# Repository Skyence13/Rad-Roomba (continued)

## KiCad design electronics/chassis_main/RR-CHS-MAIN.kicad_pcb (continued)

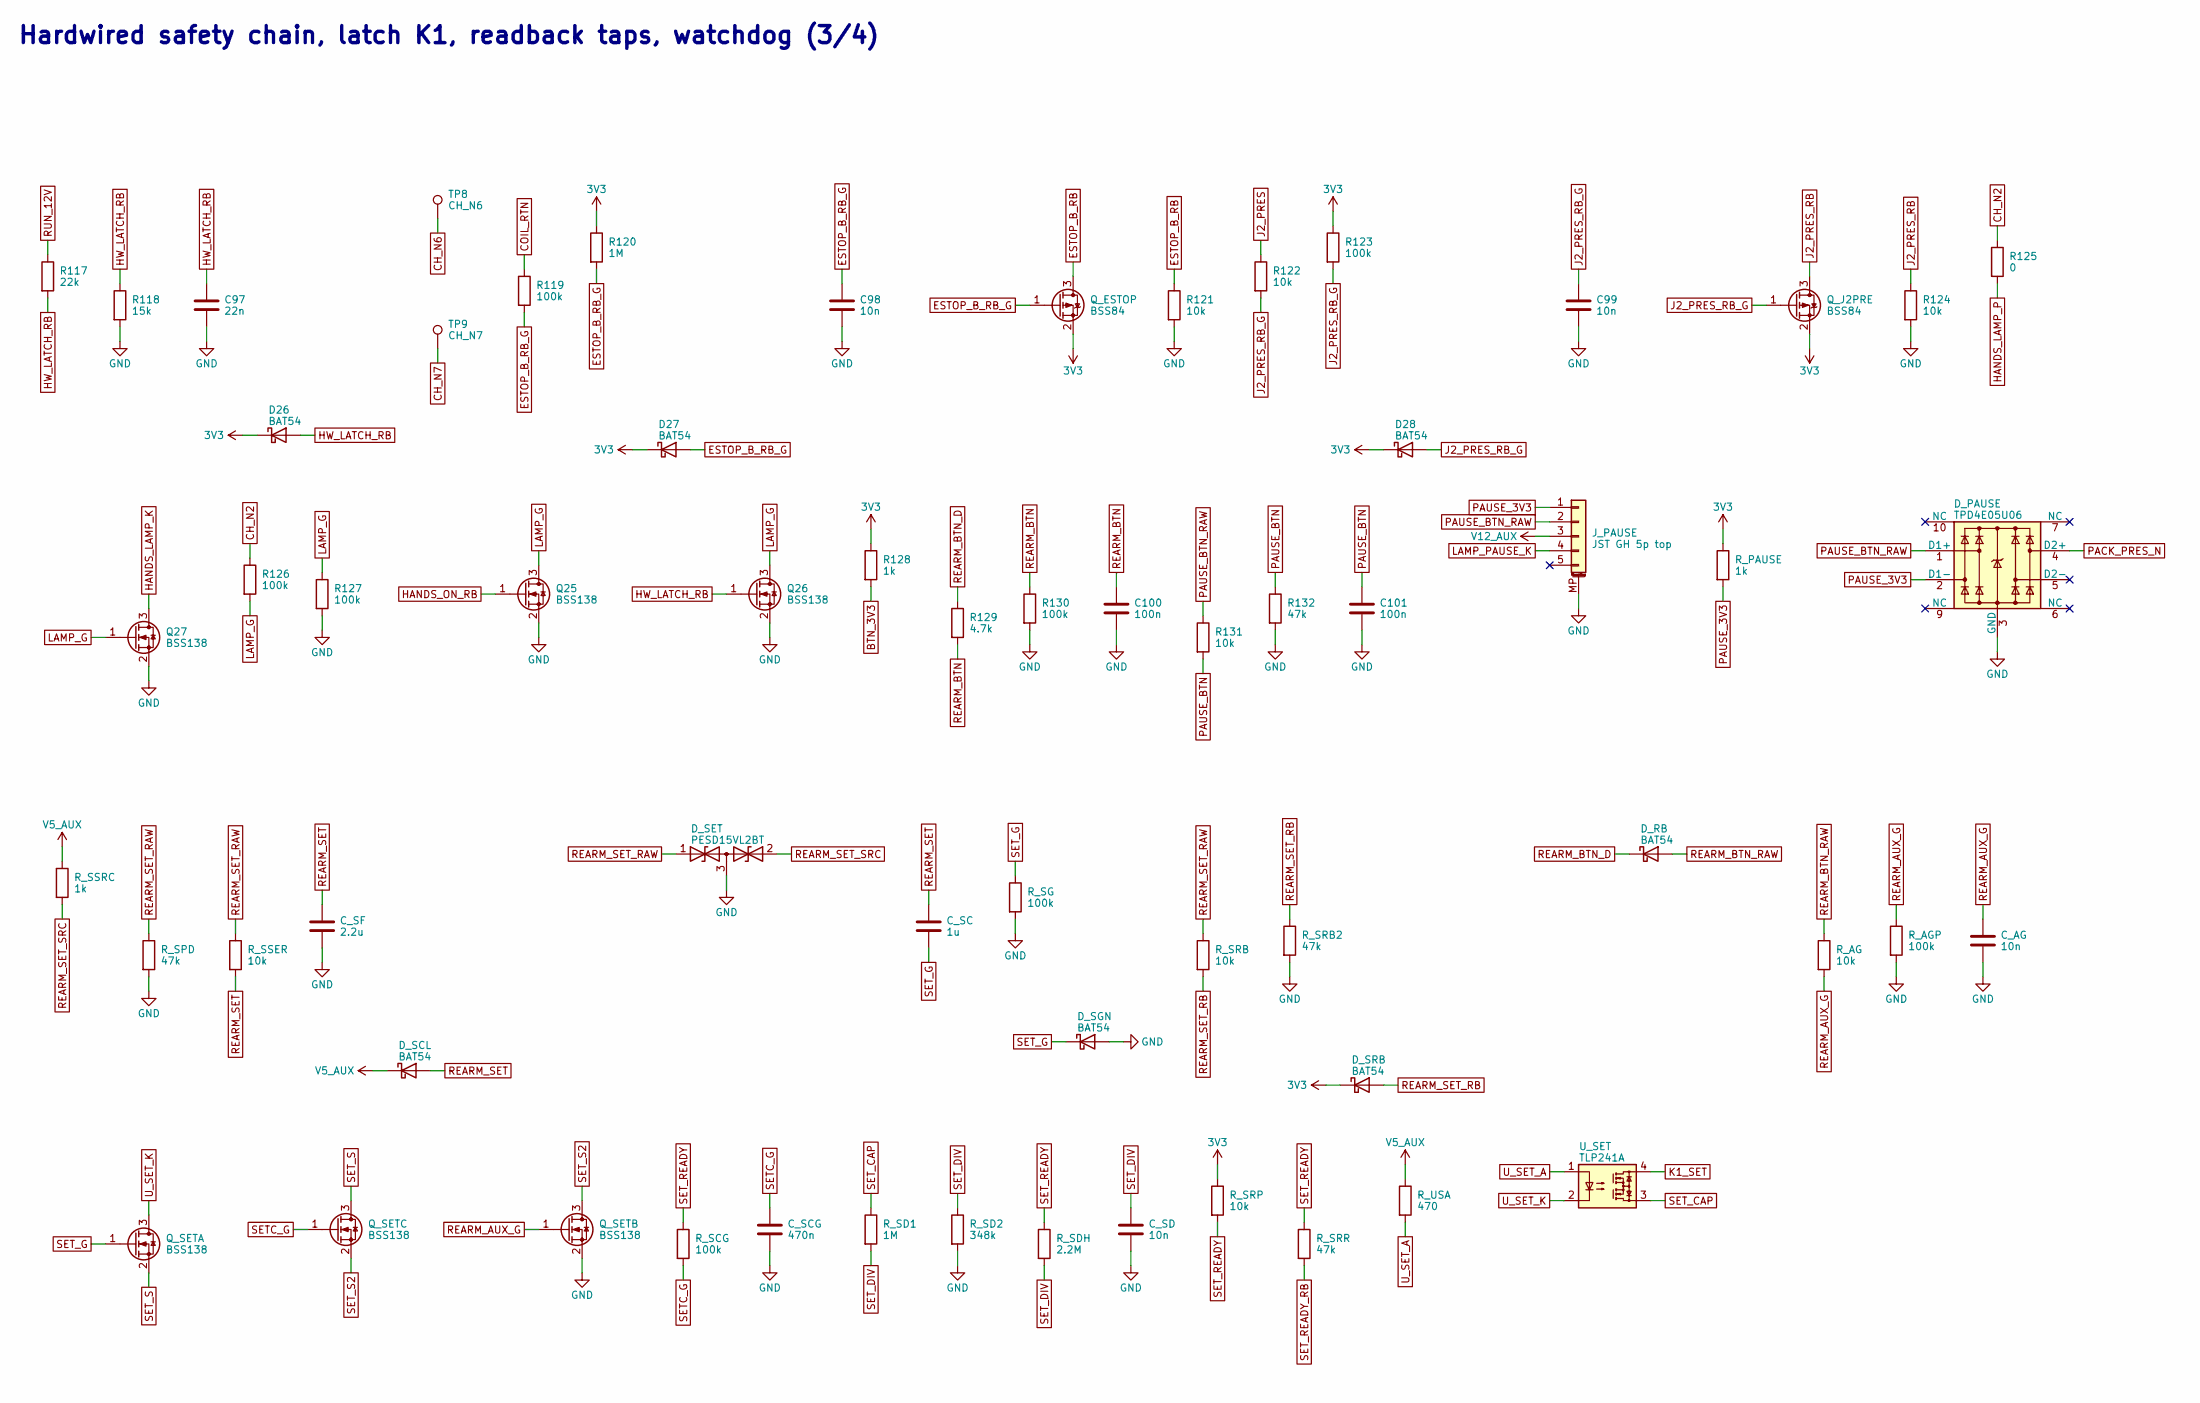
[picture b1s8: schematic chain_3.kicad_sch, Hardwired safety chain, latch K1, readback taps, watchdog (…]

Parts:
C97: 22n; C_0603_1608Metric; MPN CC0603KRX7R9BB223
C98, C99: 10n; C_0603_1608Metric; MPN CC0603KRX7R9BB103
C100, C101: 100n; C_0603_1608Metric; MPN CC0603KRX7R9BB104
C_AG: 10n; C_0603_1608Metric; MPN CC0603KRX7R9BB103
C_SC: 1u; C_0603_1608Metric; MPN GRM188R71C105KA12D
C_SCG: 470n; C_0603_1608Metric; MPN CC0603KRX7R7BB474
C_SD: 10n; C_0603_1608Metric; MPN CC0603KRX7R9BB103
C_SF: 2.2u; C_0603_1608Metric; MPN GRM188R71C225KE11D
D26, D27, D28: BAT54; D_SOD-123; MPN BAT54W-7-F
D_PAUSE: TPD4E05U06; USON-10_2.5x1.0mm_P0.5mm; MPN TPD4E05U06DQAR
D_RB: BAT54; D_SOD-123; MPN BAT54W-7-F
D_SCL: BAT54; D_SOD-123; MPN BAT54W-7-F
D_SET: PESD15VL2BT; SOT-23; MPN PESD15VL2BT,215
D_SGN: BAT54; D_SOD-123; MPN BAT54W-7-F
D_SRB: BAT54; D_SOD-123; MPN BAT54W-7-F
J_PAUSE: JST GH 5p top; JST_GH_BM05B-GHS-TBT_1x05-1MP_P1.25mm_Vertical; MPN BM05B-GHS-TBT(LF)(SN)
Q25, Q26, Q27: BSS138; SOT-23; MPN BSS138
Q_ESTOP: BSS84; SOT-23; MPN BSS84,215
Q_J2PRE: BSS84; SOT-23; MPN BSS84,215
Q_SETA: BSS138; SOT-23; MPN BSS138
Q_SETB: BSS138; SOT-23; MPN BSS138
Q_SETC: BSS138; SOT-23; MPN BSS138
R117: 22k; R_0603_1608Metric; MPN RC0603FR-0722KL
R118: 15k; R_0603_1608Metric; MPN RC0603FR-0715KL
R119, R123, R126, R127, R130: 100k; R_0603_1608Metric; MPN RC0603FR-07100KL
R120: 1M; R_0603_1608Metric; MPN RC0603FR-071ML
R121, R122, R124, R131: 10k; R_0603_1608Metric; MPN RC0603FR-0710KL
R125: 0; R_0603_1608Metric; MPN RC0603FR-070RL
R128: 1k; R_0603_1608Metric; MPN RC0603FR-071KL
R129: 4.7k; R_0603_1608Metric; MPN RC0603FR-074K7L
R132: 47k; R_0603_1608Metric; MPN RC0603FR-0747KL
R_AG: 10k; R_0603_1608Metric; MPN RC0603FR-0710KL
R_AGP: 100k; R_0603_1608Metric; MPN RC0603FR-07100KL
R_PAUSE: 1k; R_0603_1608Metric; MPN RC0603FR-071KL
R_SCG: 100k; R_0603_1608Metric; MPN RC0603FR-07100KL
R_SD1: 1M; R_0603_1608Metric; MPN RC0603FR-071ML
R_SD2: 348k; R_0603_1608Metric; MPN RC0603FR-07348KL
R_SDH: 2.2M; R_0603_1608Metric; MPN RC0603FR-072M2L
R_SG: 100k; R_0603_1608Metric; MPN RC0603FR-07100KL
R_SPD: 47k; R_0603_1608Metric; MPN RC0603FR-0747KL
R_SRB: 10k; R_0603_1608Metric; MPN RC0603FR-0710KL
R_SRB2: 47k; R_0603_1608Metric; MPN RC0603FR-0747KL
R_SRP: 10k; R_0603_1608Metric; MPN RC0603FR-0710KL
R_SRR: 47k; R_0603_1608Metric; MPN RC0603FR-0747KL
R_SSER: 10k; R_0603_1608Metric; MPN RC0603FR-0710KL
R_SSRC: 1k; R_0603_1608Metric; MPN RC0603FR-071KL
R_USA: 470; R_0603_1608Metric; MPN RC0603FR-07470RL
TP8: CH_N6; TestPoint_Keystone_5019_Miniature; MPN 5019
TP9: CH_N7; TestPoint_Keystone_5019_Miniature; MPN 5019
U_SET: TLP241A; SMDIP-4_W9.53mm; MPN TLP241A(TP1,F

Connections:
3V3: D26.1 (K), D27.1 (K), D28.1 (K), D_SRB.1 (K), Q_ESTOP.2 (S), Q_J2PRE.2 (S), R120.1, R123.1, R128.1, R_PAUSE.1, R_SRP.1; also elsewhere on the board
BTN_3V3: R128.2; also elsewhere on the board
CH_N2: R125.1, R126.1; also elsewhere on the board
CH_N6: TP8.1; also elsewhere on the board
CH_N7: TP9.1; also elsewhere on the board
COIL_RTN: R119.1; also elsewhere on the board
ESTOP_B_RB: Q_ESTOP.3 (D), R121.1; also elsewhere on the board
ESTOP_B_RB_G: C98.1, D27.2 (A), Q_ESTOP.1 (G), R119.2, R120.2
GND: C97.2, C98.2, C99.2, C100.2, C101.2, C_AG.2, C_SCG.2, C_SD.2, C_SF.2, D_PAUSE.3 (GND), D_PAUSE.8 (GND), D_SET.3 (common), D_SGN.2 (A), J_PAUSE.MP (MountPin), Q25.2 (S), Q26.2 (S), Q27.2 (S), Q_SETB.2 (S), R118.2, R121.2, R124.2, R127.2, R130.2, R132.2, R_AGP.2, R_SD2.2, R_SG.2, R_SPD.2, R_SRB2.2; also elsewhere on the board
HANDS_LAMP_K: Q27.3 (D); also elsewhere on the board
HANDS_LAMP_P: R125.2; also elsewhere on the board
HANDS_ON_RB: Q25.1 (G); also elsewhere on the board
HW_LATCH_RB: C97.1, D26.2 (A), Q26.1 (G), R117.2, R118.1; also elsewhere on the board
J2_PRES: R122.1; also elsewhere on the board
J2_PRES_RB: Q_J2PRE.3 (D), R124.1; also elsewhere on the board
J2_PRES_RB_G: C99.1, D28.2 (A), Q_J2PRE.1 (G), R122.2, R123.2
K1_SET: U_SET.4; also elsewhere on the board
LAMP_G: Q25.3 (D), Q26.3 (D), Q27.1 (G), R126.2, R127.1
LAMP_PAUSE_K: J_PAUSE.4; also elsewhere on the board
PACK_PRES_N: D_PAUSE.4 (D2+); also elsewhere on the board
PAUSE_3V3: D_PAUSE.2 (D1-), J_PAUSE.1, R_PAUSE.2
PAUSE_BTN: C101.1, R131.2, R132.1; also elsewhere on the board
PAUSE_BTN_RAW: D_PAUSE.1 (D1+), J_PAUSE.2, R131.1
REARM_AUX_G: C_AG.1, Q_SETB.1 (G), R_AG.2, R_AGP.1
REARM_BTN: C100.1, R129.2, R130.1; also elsewhere on the board
REARM_BTN_D: D_RB.1 (K), R129.1
REARM_BTN_RAW: D_RB.2 (A), R_AG.1; also elsewhere on the board
REARM_SET: C_SC.1, C_SF.1, D_SCL.2 (A), R_SSER.2
REARM_SET_RAW: D_SET.1 (A1), R_SPD.1, R_SRB.1, R_SSER.1; also elsewhere on the board
REARM_SET_RB: D_SRB.2 (A), R_SRB.2, R_SRB2.1; also elsewhere on the board
REARM_SET_SRC: D_SET.2 (A2), R_SSRC.2; also elsewhere on the board
RUN_12V: R117.1; also elsewhere on the board
SETC_G: C_SCG.1, Q_SETC.1 (G), R_SCG.2
SET_CAP: R_SD1.1, U_SET.3; also elsewhere on the board
SET_DIV: C_SD.1, R_SD1.2, R_SD2.1, R_SDH.2; also elsewhere on the board
SET_G: C_SC.2, D_SGN.1 (K), Q_SETA.1 (G), R_SG.1
SET_READY: R_SCG.1, R_SDH.1, R_SRP.2, R_SRR.1; also elsewhere on the board
SET_READY_RB: R_SRR.2; also elsewhere on the board
SET_S: Q_SETA.2 (S), Q_SETC.3 (D)
SET_S2: Q_SETB.3 (D), Q_SETC.2 (S)
U_SET_A: R_USA.2, U_SET.1
U_SET_K: Q_SETA.3 (D), U_SET.2; also elsewhere on the board
V5_AUX: D_SCL.1 (K), R_SSRC.1, R_USA.1; also elsewhere on the board
V12_AUX: J_PAUSE.3; also elsewhere on the board

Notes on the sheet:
Hardwired safety chain, latch K1, readback taps, watchdog (3/4)

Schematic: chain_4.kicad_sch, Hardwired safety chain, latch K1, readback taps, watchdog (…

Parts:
C_KR: 22n; C_0603_1608Metric; MPN CC0603KRX7R9BB223
C_LB1, C_LB2: 100n; C_0603_1608Metric; MPN CC0603KRX7R9BB104
C_N6A: 22n; C_0603_1608Metric; MPN CC0603KRX7R9BB223
C_NC: 10n; C_0603_1608Metric; MPN CC0603KRX7R9BB103
C_SDB: 1u; C_0603_1608Metric; MPN GRM188R71C105KA12D
C_U9T: 22n; C_0603_1608Metric; MPN CC0603KRX7R9BB223
C_U46, C_U47: 100n; C_0603_1608Metric; MPN CC0603KRX7R9BB104
D_AUX: PESD15VL2BT; SOT-23; MPN PESD15VL2BT,215
D_HR: 1N4148W; D_SOD-123; MPN 1N4148W-7-F
D_K1B: BAT54; D_SOD-123; MPN BAT54W-7-F
D_KR: BAT54; D_SOD-123; MPN BAT54W-7-F
D_LSR: 1N4148W; D_SOD-123; MPN 1N4148W-7-F
D_N6A: BAT54; D_SOD-123; MPN BAT54W-7-F
D_NC: BAT54; D_SOD-123; MPN BAT54W-7-F
D_RSET: 1N4148W; D_SOD-123; MPN 1N4148W-7-F
D_RUN: S1G; D_SMA; MPN S1G-13-F
D_U9T: BAT54; D_SOD-123; MPN BAT54W-7-F
Q_HSET: BSS84; SOT-23; MPN BSS84,215
Q_LB: BSS138; SOT-23; MPN BSS138
Q_LTA: BSS138; SOT-23; MPN BSS138
Q_LTB: BSS138; SOT-23; MPN BSS138
Q_SDIS: BSS138; SOT-23; MPN BSS138
Q_SDISB: BSS138; SOT-23; MPN BSS138
R_21BA: 680; R_0603_1608Metric; MPN RC0603FR-07680RL
R_GA5, R_GA7: 47k; R_0603_1608Metric; MPN RC0603FR-0747KL
R_GB7: 47k; R_0603_1608Metric; MPN RC0603FR-0747KL
R_HA: 1.5k; R_1206_3216Metric; MPN RC1206FR-071K5L
R_HS: 470; R_0603_1608Metric; MPN RC0603FR-07470RL
R_K1B: 47k; R_0603_1608Metric; MPN RC0603FR-0747KL
R_KR1: 100k; R_0603_1608Metric; MPN RC0603FR-07100KL
R_KR2: 56k; R_0603_1608Metric; MPN RC0603FR-0756KL
R_LB1, R_LB3: 10k; R_0603_1608Metric; MPN RC0603FR-0710KL
R_LB2: 30.9k; R_0603_1608Metric; MPN RC0603FR-0730K9L
R_LBG: 100k; R_0603_1608Metric; MPN RC0603FR-07100KL
R_LBR: 47k; R_0603_1608Metric; MPN RC0603FR-0747KL
R_LSA: 1.5k; R_1206_3216Metric; MPN RC1206FR-071K5L
R_LTA: 100k; R_0603_1608Metric; MPN RC0603FR-07100KL
R_LTB: 100k; R_0603_1608Metric; MPN RC0603FR-07100KL
R_N6A1: 100k; R_0603_1608Metric; MPN RC0603FR-07100KL
R_N6A2: 56k; R_0603_1608Metric; MPN RC0603FR-0756KL
R_NC1: 47k; R_0603_1608Metric; MPN RC0603FR-0747KL
R_NC2: 1M; R_0603_1608Metric; MPN RC0603FR-071ML
R_RHD: 10k; R_0603_1608Metric; MPN RC0603FR-0710KL
R_SDB1: 100k; R_0603_1608Metric; MPN RC0603FR-07100KL
R_SDB2: 56k; R_0603_1608Metric; MPN RC0603FR-0756KL
R_SDG: 100k; R_0603_1608Metric; MPN RC0603FR-07100KL
R_SDIS: 1k; R_1206_3216Metric; MPN RC1206FR-071KL
R_SV2, R_SV3, R_SV4, R_SV5, R_SV6, R_SV7, R_SV8, R_SV9, R_SV10: 220k; R_0603_1608Metric; MPN RC0603FR-07220KL
R_U9T1: 100k; R_0603_1608Metric; MPN RC0603FR-07100KL
R_U9T2: 56k; R_0603_1608Metric; MPN RC0603FR-0756KL
R_USK: 100k; R_0603_1608Metric; MPN RC0603FR-07100KL
R_WDPD: 10k; R_0603_1608Metric; MPN RC0603FR-0710KL
U21B: TLP241A; SMDIP-4_W9.53mm; MPN TLP241A(TP1,F
U46: TLV3201; SOT-23-5; MPN TLV3201AIDBVR
U_HOLD: TLP241A; SMDIP-4_W9.53mm; MPN TLP241A(TP1,F
U_LS: TLP241A; SMDIP-4_W9.53mm; MPN TLP241A(TP1,F

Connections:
3V3: C_U47.1, D_K1B.2 (A), D_KR.1 (K), D_N6A.1 (K), D_NC.1 (K), D_U9T.1 (K), R_SDG.1; also elsewhere on the board
BTN_3V3: D_AUX.2 (A2); also elsewhere on the board
CHAIN_END: D_RSET.2 (A), R_SDB1.1, R_SV2.1; also elsewhere on the board
CHN6A_RB: C_N6A.1, D_N6A.2 (A), R_N6A1.2, R_N6A2.1; also elsewhere on the board
CH_N6: U21B.4; also elsewhere on the board
CH_N6A: R_N6A1.1, R_SV9.1, U21B.3; also elsewhere on the board
COIL_RTN: U_LS.4; also elsewhere on the board
GND: C_KR.2, C_LB1.2, C_LB2.2, C_N6A.2, C_NC.2, C_SDB.2, C_U9T.2, C_U46.2, C_U47.2, D_AUX.3 (common), D_HR.2 (A), D_LSR.2 (A), Q_LB.2 (S), Q_LTA.2 (S), Q_LTB.2 (S), Q_SDIS.2 (S), Q_SDISB.2 (S), R_KR2.2, R_LB3.2, R_LBG.2, R_LTA.2, R_LTB.2, R_N6A2.2, R_NC2.2, R_RHD.2, R_SDB2.2, R_U9T2.2, R_WDPD.2, U46.2 (V-), U_HOLD.2, U_LS.2; also elsewhere on the board
HEAD_LOOP2_OK: Q_LB.1 (G), R_LBG.1, R_LBR.1, U46.1 (OUT)
HEAD_LOOP2_OK_RB: R_LBR.2; also elsewhere on the board
HEAD_LOOP_OK_IO: R_GA5.2; also elsewhere on the board
HEAD_LOOP_OK_RB: R_GA5.1; also elsewhere on the board
HOLD_A: D_HR.1 (K), R_HA.2, R_HS.2, R_SV7.1, U_HOLD.1
HSET_D: Q_HSET.3 (D), R_HS.1
HW_LATCH_G: C_U9T.1, D_U9T.2 (A), R_U9T1.2, R_U9T2.1; also elsewhere on the board
K1_BIAS: D_K1B.1 (K), R_K1B.1
K1_NC1: R_NC1.1; also elsewhere on the board
K1_RUN: R_KR1.1, R_SV3.1, U_HOLD.3; also elsewhere on the board
K1_SEAL_A: R_K1B.2; also elsewhere on the board
LAB_KEY_N_IO: R_GA7.2; also elsewhere on the board
LAB_KEY_N_RB: R_GA7.1; also elsewhere on the board
LATCH_NC_RB: C_NC.1, D_NC.2 (A), R_NC1.2, R_NC2.1; also elsewhere on the board
LATCH_RUN_RB: C_KR.1, D_KR.2 (A), R_KR1.2, R_KR2.1; also elsewhere on the board
LOOP_F: Q_LTA.3 (D); also elsewhere on the board
LOOP_FB: C_LB1.1, Q_LTB.3 (D), R_LB1.2, U46.3 (IN+)
LOOP_SNS: R_LB1.1; also elsewhere on the board
LOOP_TEST_A: Q_LTA.1 (G), R_LTA.1; also elsewhere on the board
LOOP_TEST_B: Q_LTB.1 (G), R_LTB.1; also elsewhere on the board
LOOP_VB: C_LB2.1, R_LB2.2, R_LB3.1, U46.4 (IN-)
LS_A: D_LSR.1 (K), R_LSA.2, R_SV8.1, U_LS.1
REARM_BTN_RAW: D_AUX.1 (A1); also elsewhere on the board
RELAY_RTN: R_SV6.1, U_LS.3; also elsewhere on the board
RSET_A: D_RSET.1 (K); also elsewhere on the board
RUN_12V: D_RUN.1 (K), R_SV5.1; also elsewhere on the board
RUN_HD: D_RUN.2 (A), R_HA.1, R_LSA.1, R_RHD.1, R_SV4.1, R_U9T1.1, U_HOLD.4; also elsewhere on the board
SDISB_G: C_SDB.1, Q_SDISB.1 (G), R_SDB1.2, R_SDB2.1
SDIS_G: Q_SDIS.1 (G), Q_SDISB.3 (D), R_SDG.2
SET_CAP: R_SDIS.1, R_SV10.1; also elsewhere on the board
SET_DIS: Q_SDIS.3 (D), R_SDIS.2
SVC_CHAIN_END: R_SV2.2; also elsewhere on the board
SVC_CH_N6A: R_SV9.2; also elsewhere on the board
SVC_HOLD_A: R_SV7.2; also elsewhere on the board
SVC_K1_RUN: R_SV3.2; also elsewhere on the board
SVC_LS_A: R_SV8.2; also elsewhere on the board
SVC_RELAY_RTN: R_SV6.2; also elsewhere on the board
SVC_RUN_12V: R_SV5.2; also elsewhere on the board
SVC_RUN_HD: R_SV4.2; also elsewhere on the board
SVC_SET_CAP: R_SV10.2; also elsewhere on the board
U21B_A: R_21BA.2, U21B.1
U21B_K: Q_LB.3 (D), U21B.2
U_SET_K: Q_HSET.1 (G), R_USK.2; also elsewhere on the board
V5_AUX: C_U46.1, Q_HSET.2 (S), R_21BA.1, R_LB2.1, R_USK.1, U46.5 (V+); also elsewhere on the board
WDG_STROBE: R_GB7.1, R_WDPD.1; also elsewhere on the board
WDG_STROBE_IO: R_GB7.2; also elsewhere on the board

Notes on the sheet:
Hardwired safety chain, latch K1, readback taps, watchdog (4/4)

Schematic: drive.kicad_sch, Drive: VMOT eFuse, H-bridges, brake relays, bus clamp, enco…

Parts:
C102, C112, C119, C120: 1n; C_0603_1608Metric; MPN CC0603JRNPO9BN102
C103, C104, C113: 10n; C_0603_1608Metric; MPN CC0603KRX7R9BB103
C105, C106, C107: 270u; CP_Elec_10x10.5; MPN EEHZA1V271P
C108, C109, C110, C111, C114, C116, C118, C121: 100n; C_0603_1608Metric; MPN CC0603KRX7R9BB104
C115: 22n; C_0603_1608Metric; MPN CC0603KRX7R9BB223
C117: 10u; C_1206_3216Metric; MPN GRM31CR71E106KA12L
D30: Z12; D_SOD-123; MPN BZT52C12-7-F
D31: 1N4148W; D_SOD-123; MPN 1N4148W-7-F
D32: Z20; D_SOD-123; MPN BZT52C20-7-F
D33: BAT54; D_SOD-123; MPN BAT54W-7-F
F1: 0.1A; Fuse_1206_3216Metric; MPN 1206L010YR
FB1, FB2: 50R 6A; L_1206_3216Metric; MPN BLM31SN500SN1L
F_CLAMP: 1.1A; Fuse_1812_4532Metric; MPN 1812L110/33GR
J_MOT_L: Micro-Fit 3.0 2x3 RA; Molex_Micro-Fit_3.0_43045-0600_2x03_P3.00mm_Horizontal; MPN 43045-0600
K2: G2RL-2 DC12; Relay_DPDT_Omron_G2RL-2; MPN G2RL-2 DC12
Q40: CSD18543Q3A; VSON-8_3.3x3.3mm_P0.65mm_NexFET_G0.2; MPN CSD18543Q3A
Q41: BSS138; SOT-23; MPN BSS138
R133, R144, R151: 100k; R_0603_1608Metric; MPN RC0603FR-07100KL
R134: 22k; R_0603_1608Metric; MPN RC0603FR-0722KL
R135: 237; R_0603_1608Metric; MPN RC0603FR-07237RL
R136: 1.5k; R_0603_1608Metric; MPN RC0603FR-071K5L
R137, R140, R141, R142, R143, R147, R156, R157, R158, R163, R164, R165, R166: 10k; R_0603_1608Metric; MPN RC0603FR-0710KL
R138: 1k; R_1206_3216Metric; MPN RC1206FR-071KL
R139: 47k; R_0603_1608Metric; MPN RC0603FR-0747KL
R145: 19.1k; R_0603_1608Metric; MPN RC0603FR-0719K1L
R146: 3.3M; R_0603_1608Metric; MPN RC0603FR-073M3L
R148: 4.7k; R_0603_1608Metric; MPN RC0603FR-074K7L
R149, R150: 9.1; R_2512_6332Metric; MPN CRM2512-JW-9R1ELF
R152: 33k; R_0603_1608Metric; MPN RC0603FR-0733KL
R153: 2.49k; R_0603_1608Metric; MPN RT0603BRD072K49L
R154: 1k; R_0603_1608Metric; MPN RC0603FR-071KL
R155: 0; R_0603_1608Metric; MPN RC0603FR-070RL
R159, R160: 4.7k; R_0805_2012Metric; MPN RC0805FR-074K7L
R161: 1; R_2512_6332Metric; MPN CRM2512-FX-1R00ELF
R162: 2.2k; R_0805_2012Metric; MPN RC0805FR-072K2L
TP10: U8_IMON; TestPoint_Keystone_5019_Miniature; MPN 5019
TP11: VMOT_PG; TestPoint_Keystone_5019_Miniature; MPN 5019
U5: DRV8874; HTSSOP-16-1EP_4.4x5mm_P0.65mm_EP3.4x5mm_Mask2.46x2.31mm; MPN DRV8874PWPR
U8: TPS25982; TI_TPS25982_VQFN-24_4x4mm_SplitPad_PLACEHOLDER; MPN TPS259822ONRGER
U9: 74LVC1G08; SOT-23-5; MPN SN74LVC1G08DBVR
U33, U35: LM2903B; SOIC-8_3.9x4.9mm_P1.27mm; MPN LM2903BIDR
U34: LM4040-2.5; SOT-23; MPN LM4040C25IDBZR
U37: 74LVC2G17; SOT-23-6; MPN SN74LVC2G17DBVR
W1: pads; WirePads_2x2.5mm_P5.0mm; MPN WIRE-PADS; not fitted

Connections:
3V3: C109.1, D33.2 (A), R137.1, R156.1, R165.1, R166.1, U5.16 (PMODE), U9.5 (VCC); also elsewhere on the board
BIAS_L: D33.1 (K), R162.1
BRAKE_L_ISO: Q41.1 (G), R165.2, U35.1, U35.7
BRAKE_L_RB: Q41.3 (D), R166.2; also elsewhere on the board
BRK_L_A: K2.12, R161.1
BRK_L_B: K2.22, R161.2
BRK_THR: U35.3 (+), U35.5 (+); also elsewhere on the board
BUS_CLAMP_ACTIVE: R151.2, R152.1; also elsewhere on the board
CLAMP_DIV: C112.1, R144.2, R145.1, R146.2, U33.3 (+)
CLAMP_F: F_CLAMP.2, R149.1, R150.1, W1.1
CLAMP_G: Q40.4 (G), R146.1, R147.2, R151.1, U33.1; also elsewhere on the board
CLAMP_R: Q40.5 (D), R149.2, R150.2, W1.2
CLAMP_REF: C111.1, R143.2, U33.2 (-), U33.6 (-), U34.1 (K)
CLAMP_VG: D30.1 (K), R147.1, R148.2
DRV_L_NFAULT: R156.2, U5.4 (nFAULT); also elsewhere on the board
DRV_NSLEEP: R141.1, U9.1; also elsewhere on the board
DRV_NSLEEP_G: R142.1, U5.3 (nSLEEP), U9.4; also elsewhere on the board
ENCC_L_A: J_MOT_L.5; also elsewhere on the board
ENCC_L_B: J_MOT_L.6; also elsewhere on the board
ENC_L_5V: C121.1, F1.2, J_MOT_L.3; also elsewhere on the board
ENC_L_A: U37.6; also elsewhere on the board
ENC_L_B: U37.4; also elsewhere on the board
GND: C102.2, C103.2, C104.2, C105.2, C106.2, C107.2, C108.2, C109.2, C110.2, C111.2, C112.2, C113.2, C116.2, C117.2, C118.2, C119.2, C120.2, C121.2, D30.2 (A), J_MOT_L.4, Q40.1 (S), Q40.2 (S), Q40.3 (S), Q41.2 (S), R134.2, R135.2, R136.2, R138.2, R140.2, R141.2, R142.2, R145.2, R152.2, R153.2, R155.2, R157.2, R158.2, R159.2, R160.2, U5.9 (PGND), U5.15 (GND), U5.17 (EP), U8.4 (GND), U8.5 (GND), U8.10 (RETRY_DLY), U8.11 (NRETRY), U8.12 (LDSTRT), U8.14 (GND), U8.26 (GND_PAD), U9.3 (GND), U33.4 (V-), U34.2 (A), U35.4 (V-); also elsewhere on the board
HW_LATCH_G: U9.2; also elsewhere on the board
IPROPI_L: C113.1, R154.2; also elsewhere on the board
IPROPI_L_RAW: R153.1, R154.1, U5.6 (IPROPI)
K2_CL: D31.1 (K), D32.1 (K)
MOTC_L_A: C119.1, FB1.2, J_MOT_L.1
MOTC_L_B: C120.1, FB2.2, J_MOT_L.2
MOT_L_A: FB1.1, K2.11, R162.2
MOT_L_B: FB2.1, K2.21
MOT_L_IN1: R157.1, U5.1 (EN/IN1); also elsewhere on the board
MOT_L_IN2: R158.1, U5.2 (PH/IN2); also elsewhere on the board
OUT1_L: K2.14, R159.1, R163.1, U5.8 (OUT1)
OUT2_L: K2.24, R160.1, R164.1, U5.10 (OUT2)
RELAY_RTN: D31.2 (A), K2.A2; also elsewhere on the board
RUN_12V: D32.2 (A), K2.A1; also elsewhere on the board
RUN_HD: R133.1; also elsewhere on the board
SET_DIV: U33.5 (+); also elsewhere on the board
SET_READY: U33.7; also elsewhere on the board
U5_CPH: C115.1, U5.13 (CPH)
U5_CPL: C115.2, U5.14 (CPL)
U5_IMODE: R155.1, U5.7 (IMODE)
U5_VCP: C114.1, U5.12 (VCP)
U8_DVDT: C104.1, U8.15 (dVdt)
U8_EN: C102.1, R133.2, R134.1, U8.6 (EN/UVLO)
U8_ILIM: R135.1, U8.8 (ILIM)
U8_IMON: R136.1, TP10.1, U8.9 (IMON)
U8_ITMR: C103.1, U8.7 (ITIMER)
U35_A: R163.2, U35.2 (-)
U35_B: R164.2, U35.6 (-)
U37_A: U37.1; also elsewhere on the board
U37_B: U37.3; also elsewhere on the board
V5_AUX: C118.1, F1.1, U35.8 (V+); also elsewhere on the board
VBAT_SW: C110.1, R143.1, R148.1, U8.1 (IN), U8.2 (IN), U8.3 (IN), U8.16 (IN), U8.25 (IN_PAD), U33.8 (V+); also elsewhere on the board
VMOT: C105.1, C106.1, C107.1, C114.2, C116.1, C117.1, F_CLAMP.1, R138.1, R139.1, R144.1, U5.11 (VM), U8.17 (OUT), U8.18 (OUT), U8.19 (OUT), U8.20 (OUT), U8.21 (OUT), U8.22 (OUT), U8.23 (OUT), U8.24 (OUT); also elsewhere on the board
VMOT_PG: R137.2, TP11.1, U8.13 (PG)
VMOT_SENSE: C108.1, R139.2, R140.1; also elsewhere on the board
VREF_3V0: U5.5 (VREF); also elsewhere on the board

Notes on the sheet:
Drive: VMOT eFuse, H-bridges, brake relays, bus clamp, encoders (1/2)

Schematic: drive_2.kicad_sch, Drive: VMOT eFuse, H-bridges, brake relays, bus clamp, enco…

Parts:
C122, C126, C128, C130, C133, C134, C137: 100n; C_0603_1608Metric; MPN CC0603KRX7R9BB104
C123, C124, C131, C132, C135, C136: 1n; C_0603_1608Metric; MPN CC0603JRNPO9BN102
C125: 10n; C_0603_1608Metric; MPN CC0603KRX7R9BB103
C127: 22n; C_0603_1608Metric; MPN CC0603KRX7R9BB223
C129: 10u; C_1206_3216Metric; MPN GRM31CR71E106KA12L
D34: 1N4148W; D_SOD-123; MPN 1N4148W-7-F
D35: Z20; D_SOD-123; MPN BZT52C20-7-F
D36: BAT54; D_SOD-123; MPN BAT54W-7-F
D37: TPD4E05U06; USON-10_2.5x1.0mm_P0.5mm; MPN TPD4E05U06DQAR
F2: 0.1A; Fuse_1206_3216Metric; MPN 1206L010YR
FB3, FB4: 50R 6A; L_1206_3216Metric; MPN BLM31SN500SN1L
J_MOT_R: Micro-Fit 3.0 2x3 RA; Molex_Micro-Fit_3.0_43045-0600_2x03_P3.00mm_Horizontal; MPN 43045-0600
K3: G2RL-2 DC12; Relay_DPDT_Omron_G2RL-2; MPN G2RL-2 DC12
Q42: BSS138; SOT-23; MPN BSS138
R167, R169, R174, R175, R176, R181, R182, R183, R184, R185, R187: 10k; R_0603_1608Metric; MPN RC0603FR-0710KL
R168, R170, R186, R188: 4.7k; R_0603_1608Metric; MPN RC0603FR-074K7L
R171: 2.49k; R_0603_1608Metric; MPN RT0603BRD072K49L
R172: 1k; R_0603_1608Metric; MPN RC0603FR-071KL
R173: 0; R_0603_1608Metric; MPN RC0603FR-070RL
R177, R178: 4.7k; R_0805_2012Metric; MPN RC0805FR-074K7L
R179: 1; R_2512_6332Metric; MPN CRM2512-FX-1R00ELF
R180: 2.2k; R_0805_2012Metric; MPN RC0805FR-072K2L
R189: 14k; R_0603_1608Metric; MPN RC0603FR-0714KL
R190: 590; R_0603_1608Metric; MPN RC0603FR-07590RL
U6: DRV8874; HTSSOP-16-1EP_4.4x5mm_P0.65mm_EP3.4x5mm_Mask2.46x2.31mm; MPN DRV8874PWPR
U36: LM2903B; SOIC-8_3.9x4.9mm_P1.27mm; MPN LM2903BIDR
U37, U38: 74LVC2G17; SOT-23-6; MPN SN74LVC2G17DBVR

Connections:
3V3: C122.1, C134.1, D36.2 (A), R174.1, R183.1, R184.1, U6.16 (PMODE), U37.5 (VCC), U38.5 (VCC); also elsewhere on the board
BIAS_R: D36.1 (K), R180.1
BRAKE_R_ISO: Q42.1 (G), R183.2, U36.1, U36.7
BRAKE_R_RB: Q42.3 (D), R184.2; also elsewhere on the board
BRK_R_A: K3.12, R179.1
BRK_R_B: K3.22, R179.2
BRK_THR: C137.1, R189.2, R190.1, U36.3 (+), U36.5 (+); also elsewhere on the board
DRV_NSLEEP_G: U6.3 (nSLEEP); also elsewhere on the board
DRV_R_NFAULT: R174.2, U6.4 (nFAULT); also elsewhere on the board
ENCC_L_A: D37.1 (D1+), R167.2, R168.1; also elsewhere on the board
ENCC_L_B: D37.2 (D1-), R169.2, R170.1; also elsewhere on the board
ENCC_R_A: D37.4 (D2+), J_MOT_R.5, R185.2, R186.1
ENCC_R_B: D37.5 (D2-), J_MOT_R.6, R187.2, R188.1
ENC_L_5V: R167.1, R169.1; also elsewhere on the board
ENC_R_5V: C133.1, F2.2, J_MOT_R.3, R185.1, R187.1
ENC_R_A: U38.6; also elsewhere on the board
ENC_R_B: U38.4; also elsewhere on the board
GND: C122.2, C123.2, C124.2, C125.2, C128.2, C129.2, C130.2, C131.2, C132.2, C133.2, C134.2, C135.2, C136.2, C137.2, D37.3 (GND), D37.8 (GND), J_MOT_R.4, Q42.2 (S), R171.2, R173.2, R175.2, R176.2, R177.2, R178.2, R190.2, U6.9 (PGND), U6.15 (GND), U6.17 (EP), U36.4 (V-), U37.2 (GND), U38.2 (GND); also elsewhere on the board
IPROPI_R: C125.1, R172.2; also elsewhere on the board
IPROPI_R_RAW: R171.1, R172.1, U6.6 (IPROPI)
K3_CL: D34.1 (K), D35.1 (K)
MOTC_R_A: C131.1, FB3.2, J_MOT_R.1
MOTC_R_B: C132.1, FB4.2, J_MOT_R.2
MOT_R_A: FB3.1, K3.11, R180.2
MOT_R_B: FB4.1, K3.21
MOT_R_IN1: R175.1, U6.1 (EN/IN1); also elsewhere on the board
MOT_R_IN2: R176.1, U6.2 (PH/IN2); also elsewhere on the board
OUT1_R: K3.14, R177.1, R181.1, U6.8 (OUT1)
OUT2_R: K3.24, R178.1, R182.1, U6.10 (OUT2)
RELAY_RTN: D34.2 (A), K3.A2; also elsewhere on the board
RUN_12V: D35.2 (A), K3.A1; also elsewhere on the board
U6_CPH: C127.1, U6.13 (CPH)
U6_CPL: C127.2, U6.14 (CPL)
U6_IMODE: R173.1, U6.7 (IMODE)
U6_VCP: C126.1, U6.12 (VCP)
U36_A: R181.2, U36.2 (-)
U36_B: R182.2, U36.6 (-)
U37_A: C123.1, R168.2; also elsewhere on the board
U37_B: C124.1, R170.2; also elsewhere on the board
U38_A: C135.1, R186.2, U38.1
U38_B: C136.1, R188.2, U38.3
V5_AUX: C130.1, F2.1, R189.1, U36.8 (V+); also elsewhere on the board
VMOT: C126.2, C128.1, C129.1, U6.11 (VM); also elsewhere on the board
VREF_3V0: U6.5 (VREF); also elsewhere on the board

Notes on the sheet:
Drive: VMOT eFuse, H-bridges, brake relays, bus clamp, encoders (2/2)

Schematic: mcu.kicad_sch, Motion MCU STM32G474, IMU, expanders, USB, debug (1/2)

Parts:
C138, C139, C140, C141, C143, C147, C149, C150, C151: 100n; C_0603_1608Metric; MPN CC0603KRX7R9BB104
C142: 4.7u; C_0805_2012Metric; MPN GRM21BR71C475KA73L
C144: 1u; C_0603_1608Metric; MPN GRM188R71C105KA12D
C145, C146: 10p; C_0603_1608Metric; MPN CC0603JRNPO9BN100
C148: 10n; C_0603_1608Metric; MPN CC0603KRX7R9BB103
J_DBG: JST GH 4p top; JST_GH_BM04B-GHS-TBT_1x04-1MP_P1.25mm_Vertical; MPN BM04B-GHS-TBT(LF)(SN)
J_SWD: Cortex debug 2x5 1.27; PinHeader_2x05_P1.27mm_Vertical_SMD; MPN FTSH-105-01-L-DV-K
J_USB_MCU: JST GH 5p top; JST_GH_BM05B-GHS-TBT_1x05-1MP_P1.25mm_Vertical; MPN BM05B-GHS-TBT(LF)(SN)
LED1: green; LED_0603_1608Metric; MPN 150060GS75000
R191, R197, R198: 220; R_0603_1608Metric; MPN RC0603FR-07220RL
R192, R195, R199, R202, R203, R204: 10k; R_0603_1608Metric; MPN RC0603FR-0710KL
R193, R194: 1k; R_0603_1608Metric; MPN RC0603FR-071KL
R196: 100; R_0603_1608Metric; MPN RC0603FR-07100RL
R200: 1M; R_0603_1608Metric; MPN RC0603FR-071ML
R201, R205: 33; R_0603_1608Metric; MPN RC0603FR-0733RL
SW1: RESET; SW_Tactile_SPST_NO_Straight_CK_PTS636Sx25SMTRLFS; MPN PTS636 SM25F SMTR LFS
SW2: DFU; SW_Tactile_SPST_NO_Straight_CK_PTS636Sx25SMTRLFS; MPN PTS636 SM25F SMTR LFS
U20M: STM32G474RET6; LQFP-64_10x10mm_P0.5mm; MPN STM32G474RET6
U41: USBLC6-2SC6; SOT-23-6; MPN USBLC6-2SC6
U42: BMI088; Bosch_LGA-16_4.5x3mm_P0.5mm_ClockwisePinNumbering; MPN BMI088
U43: MCP23S17; SSOP-28_5.3x10.2mm_P0.65mm; MPN MCP23S17-E/SS
Y1: 8MHz; Crystal_SMD_3225-4Pin_3.2x2.5mm; MPN NX3225GD-8.000M-STD-CRA-3

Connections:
3V3: C138.1, C139.1, C140.1, C141.1, C142.1, C149.1, C150.1, C151.1, J_SWD.1 (VTref), R192.1, R196.1, R199.1, R202.1, R203.1, R204.1, SW2.1, U20M.1 (VBAT), U20M.16 (VDD), U20M.32 (VDD), U20M.48 (VDD), U20M.64 (VDD), U41.5 (VBUS), U42.3 (VDD), U42.11 (VDDIO), U43.9 (VDD); also elsewhere on the board
3V3A: U20M.29 (VDDA); also elsewhere on the board
ARM_PERMIT: U20M.30 (PB10); also elsewhere on the board
BODY_BUMPER_L_RB: U43.1 (GPB0); also elsewhere on the board
BODY_BUMPER_R_RB: U43.2 (GPB1); also elsewhere on the board
BOOT0_LED_STAT: R193.2, R194.1, R195.1, U20M.61 (PB8)
BOOT0_SW: R193.1, SW2.2
BRAKE_L_RB: U20M.3 (PC14); also elsewhere on the board
BRAKE_R_RB: U20M.4 (PC15); also elsewhere on the board
BUZZER: U20M.26 (PB2); also elsewhere on the board
CHG_COVER_RB: U43.23 (GPA2); also elsewhere on the board
CHG_PLUG_LINK_RB: U43.24 (GPA3); also elsewhere on the board
CHS_HTR_EN: U20M.37 (PB15); also elsewhere on the board
DBG_3V3: J_DBG.1, R196.2
DBG_RX: R198.2, R199.2, U20M.53 (PC11)
DBG_RX_C: J_DBG.3, R198.1; also elsewhere on the board
DBG_TX: R197.1, U20M.52 (PC10)
DBG_TX_C: J_DBG.2, R197.2; also elsewhere on the board
DRV_L_NFAULT: U43.5 (GPB4); also elsewhere on the board
DRV_NSLEEP: U20M.44 (PA10); also elsewhere on the board
DRV_R_NFAULT: U43.6 (GPB5); also elsewhere on the board
ENC_L_A: U20M.59 (PB6); also elsewhere on the board
ENC_L_B: U20M.60 (PB7); also elsewhere on the board
ENC_R_A: U20M.57 (PB4); also elsewhere on the board
ENC_R_B: U20M.58 (PB5); also elsewhere on the board
ESTOP_A_RB: U20M.34 (PB12); also elsewhere on the board
ESTOP_B_RB: U20M.35 (PB13); also elsewhere on the board
GND: C138.2, C139.2, C140.2, C141.2, C142.2, C143.2, C144.2, C145.2, C146.2, C147.2, C148.2, C149.2, C150.2, C151.2, J_DBG.4, J_DBG.MP (MountPin), J_SWD.3 (GND), J_SWD.5 (GND), J_SWD.9 (GNDDetect), J_USB_MCU.4, J_USB_MCU.MP (MountPin), LED1.1 (K), R195.2, R200.2, SW1.2, U20M.15 (VSS), U20M.27 (VSSA), U20M.31 (VSS), U20M.47 (VSS), U20M.63 (VSS), U41.2 (GND), U42.2 (GNDA), U42.4 (GNDA), U42.6 (GNDIO), U42.7 (PS), U43.10 (VSS), U43.15 (A0), U43.16 (A1), U43.17 (A2), Y1.2 (G), Y1.4 (G); also elsewhere on the board
HANDS_ON_RB: U43.22 (GPA1); also elsewhere on the board
HEAD_DOCK_RB: U43.25 (GPA4); also elsewhere on the board
HEAD_HTR_EN: U20M.36 (PB14); also elsewhere on the board
HEAD_LOOP_OK_IO: U43.26 (GPA5); also elsewhere on the board
HEAD_LOOP_SENSE: U20M.9 (PC1); also elsewhere on the board
HEAD_LOOP_SHORT_RB: U43.27 (GPA6); also elsewhere on the board
HEAD_PRES_ID_ADC: U20M.8 (PC0); also elsewhere on the board
HW_LATCH_RB: U20M.55 (PD2); also elsewhere on the board
I2C_SYS_SCL: U20M.43 (PA9); also elsewhere on the board
I2C_SYS_SDA: U20M.42 (PA8); also elsewhere on the board
I2C_TOF_SCL: U20M.51 (PA15); also elsewhere on the board
I2C_TOF_SDA: U20M.62 (PB9); also elsewhere on the board
IMU_CS_ACC_N: R202.2, U20M.18 (PA4), U42.14 (~CSB1)
IMU_CS_GYR_N: R203.2, U20M.23 (PC5), U42.5 (~CSB2)
IMU_SDO: R201.1, U42.10 (SDO2), U42.15 (SDO1)
IOXA_SO: R205.1, U43.14 (SO)
IOX_A_CS_N: R204.2, U20M.24 (PB0), U43.11 (~CS)
IPROPI_L: U20M.12 (PA0); also elsewhere on the board
IPROPI_R: U20M.13 (PA1); also elsewhere on the board
J2_PRES_RB: U20M.54 (PC12); also elsewhere on the board
LAB_KEY_N_IO: U43.28 (GPA7); also elsewhere on the board
LED_STAT_A: LED1.2 (A), R194.2
MCUC_USB_DM: J_USB_MCU.2, U41.1 (I/O1)
MCUC_USB_DP: J_USB_MCU.3, U41.3 (I/O2)
MCU_USB_DM: U20M.45 (PA11), U41.6 (I/O1)
MCU_USB_DP: U20M.46 (PA12), U41.4 (I/O2)
MODE_RUN_RB: U43.21 (GPA0); also elsewhere on the board
MOT_L_IN1: U20M.38 (PC6); also elsewhere on the board
MOT_L_IN2: U20M.39 (PC7); also elsewhere on the board
MOT_R_IN1: U20M.40 (PC8); also elsewhere on the board
MOT_R_IN2: U20M.41 (PC9); also elsewhere on the board
NRST: C147.1, J_SWD.10 (~RESET), R192.2, SW1.1, U20M.7 (PG10), U43.18 (~RESET); also elsewhere on the board
NTC_BAY_ADC: U20M.10 (PC2); also elsewhere on the board
NTC_BOARD_ADC: U20M.22 (PC4); also elsewhere on the board
NTC_PACK_ADC: U20M.11 (PC3); also elsewhere on the board
OSC_IN: C145.1, U20M.5 (PF0), Y1.1
OSC_OUT: R191.1, U20M.6 (PF1)
OSC_XO: C146.1, R191.2, Y1.3
PAUSE_BTN: U43.4 (GPB3); also elsewhere on the board
REARM_BTN: U43.3 (GPB2); also elsewhere on the board
REARM_SET_RB: U43.7 (GPB6); also elsewhere on the board
SPI1_MISO: R201.2, R205.2, U20M.20 (PA6); also elsewhere on the board
SPI1_MOSI: U20M.21 (PA7), U42.9 (SDI/SDA), U43.13 (SI); also elsewhere on the board
SPI1_SCK: U20M.19 (PA5), U42.8 (SCK/SCL), U43.12 (SCK); also elsewhere on the board
SWCLK: J_SWD.4 (SWCLK/TCK), U20M.50 (PA14)
SWDIO: J_SWD.2 (SWDIO/TMS), U20M.49 (PA13)
SWO_SPARE: J_SWD.6 (SWO/TDO), U20M.56 (PB3); also elsewhere on the board
USB_SHLD: C148.1, J_USB_MCU.5, R200.1; also elsewhere on the board
V5_SENSE: U20M.25 (PB1); also elsewhere on the board
VBAT_SENSE: U20M.17 (PA3); also elsewhere on the board
VMOT_SENSE: U20M.14 (PA2); also elsewhere on the board
VREF_3V0: C143.1, C144.1, U20M.28 (VREF+); also elsewhere on the board
WDG_OK_RB: U20M.2 (PC13); also elsewhere on the board
WDG_STROBE: U20M.33 (PB11); also elsewhere on the board
WDG_STROBE_IO: U43.8 (GPB7); also elsewhere on the board

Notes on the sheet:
Motion MCU STM32G474, IMU, expanders, USB, debug (1/2)
S2-05: U42 (BMI088) GNDA on pins 2 and 4 (stock symbol). Pin use = firmware/chassis/pinmap.yaml.
